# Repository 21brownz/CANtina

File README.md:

# CANtina

CANtina is a CAN bus star PCB inspired by Team 5883's PCBs and developed by 6502 DARC SIDE's Electrical Subteam.
* CANtina utilizes Weidmuller LSF-SMT-3.5 push-to-connect terminal blocks to allow you to easily connect and disconnect devices.
* CANtina has built in resistors in order to allow you to maintain CANbus's required impedance.
* CANtina is Open Source!

## Warning:
Star topology can be very fussy. It violates the ISO 11898 standard and is not officially supported by any manufacturer. Team 6502 does not reccomend star topology for any applications that are not for the purposes of education, research, or hardware and software development. **Please be careful!**

### Questions or Comments
If you have any questions or comments, please feel free to drop me a line on Chief Delphi @21brownz.

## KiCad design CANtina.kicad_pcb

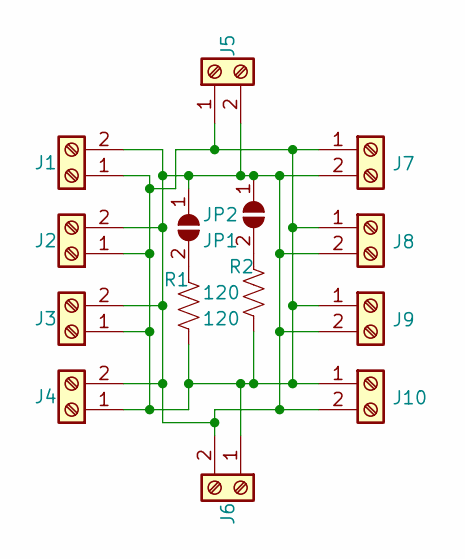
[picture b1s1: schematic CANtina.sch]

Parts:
J1, J2, J3, J4, J5, J6, J7, J8, J9, J10: Screw_Terminal_01x02; LSF-SMT-3.5-2
JP1, JP2: SolderJumper_2_Open; JUMPER-SOLDER-3mm
R1, R2: 120; Resistors_Vertical_10mm

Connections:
unnamed: J1.1, J2.1, J3.1, J4.1, J5.1, J6.1, J7.1, J8.1, J9.1, J10.1, R1.2, R2.2
unnamed: J1.2, J2.2, J3.2, J4.2, J5.2, J6.2, J7.2, J8.2, J9.2, J10.2, JP1.1 (A), JP2.1 (A)
unnamed: JP1.2 (B), R1.1
unnamed: JP2.2 (B), R2.1

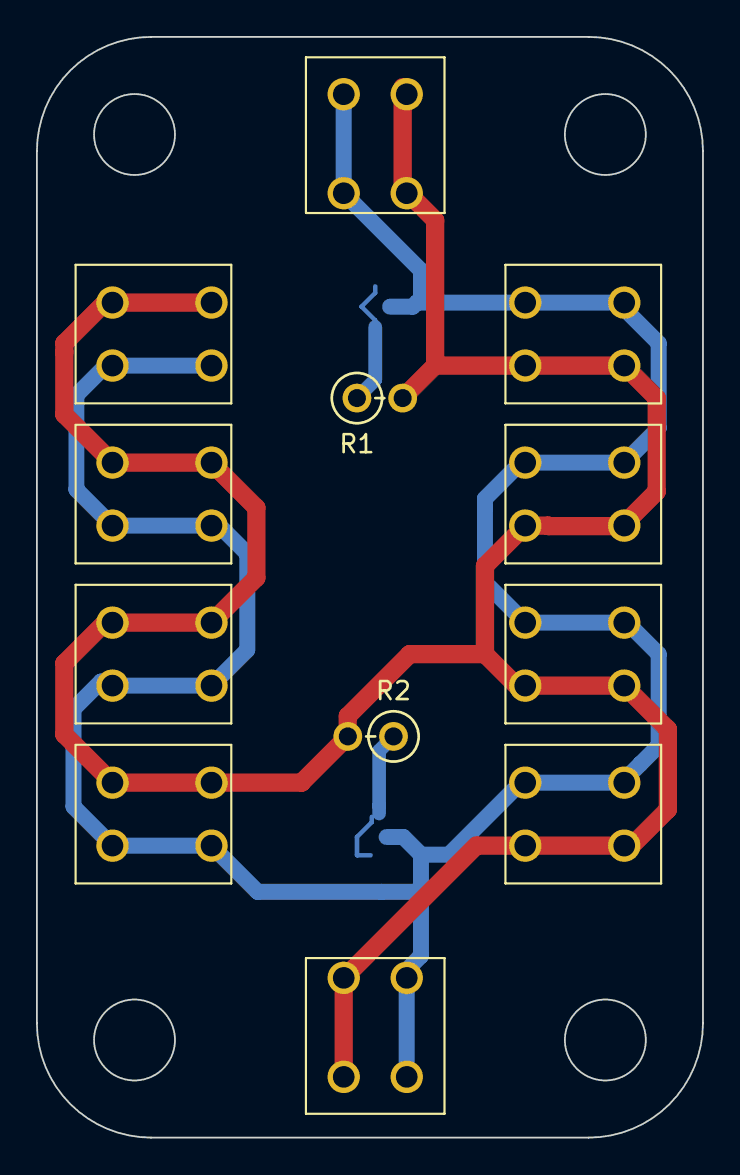
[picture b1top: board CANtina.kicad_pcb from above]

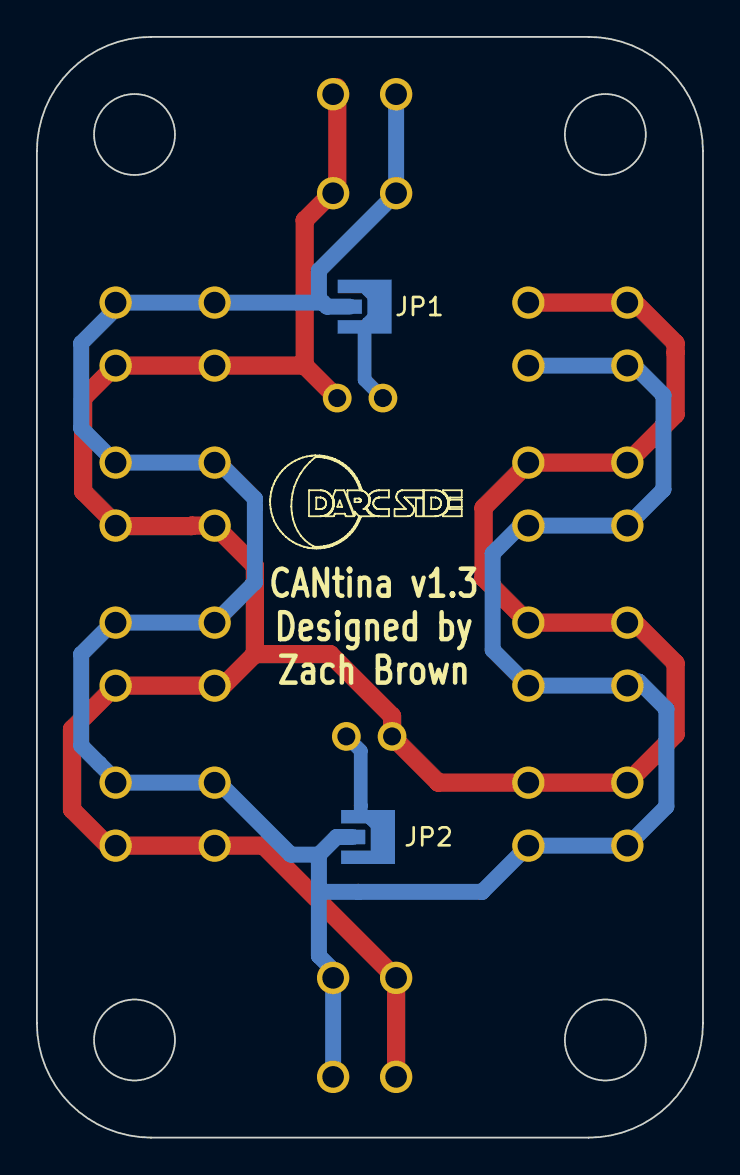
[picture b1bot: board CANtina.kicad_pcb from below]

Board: 2 copper layers, 37.0 x 61.2 mm, 14 parts (2 on the bottom side), 4 nets.

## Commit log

2019-10-04 added pcb files
2019-10-04 Created .gitignore
2019-10-04 cleaned up
2019-10-04 updated gitignore
2019-10-04 cleaned up and added images
2019-10-04 readme grammar
2019-10-04 updated info
2019-10-07 added image to readme
2020-02-09 fixed pcb traces
